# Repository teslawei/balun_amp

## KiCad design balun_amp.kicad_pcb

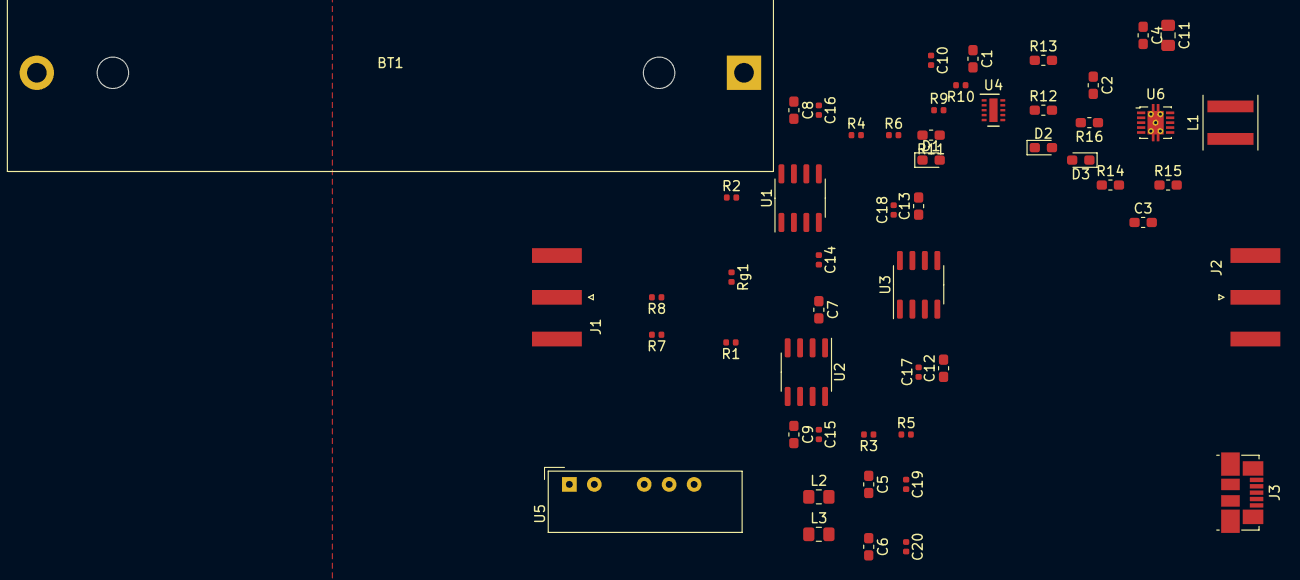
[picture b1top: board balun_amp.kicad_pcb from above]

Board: 4 copper layers, 53 parts (0 on the bottom side), 31 nets.

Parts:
BT1: Battery_Cell; BatteryHolder_MPD_BH-18650-PC2
C1, C2, C3, C5, C6: 10u; C_0603_1608Metric_Pad1.05x0.95mm_HandSolder
C4: 2.2u; C_0603_1608Metric_Pad1.05x0.95mm_HandSolder
C7, C8, C9, C12, C13: 1u; C_0603_1608Metric_Pad1.05x0.95mm_HandSolder
C10: 100n; C_0402_1005Metric
C11: 47u; C_0805_2012Metric_Pad1.15x1.40mm_HandSolder
C14, C15, C16, C17, C18, C19, C20: 10n; C_0402_1005Metric
D1, D2, D3: LED; LED_0603_1608Metric_Pad1.05x0.95mm_HandSolder
J1: Input; SMA_Amphenol_132289_EdgeMount
J2: Output; SMA_Amphenol_132289_EdgeMount
J3: USB_B_Micro; USB_Micro-B_Molex_47346-0001
L1: 6.8uH; L_Coilcraft_XAL5030
L2, L3: 150u; L_0805_2012Metric_Pad1.15x1.40mm_HandSolder
R1, R2, R3, R4, R5, R6, R7, R8: R; R_0402_1005Metric
R9: 2k; R_0402_1005Metric
R10: 1k; R_0402_1005Metric
R11, R13, R15, R16: 1.5k; R_0603_1608Metric_Pad1.05x0.95mm_HandSolder
R12: 10k; R_0603_1608Metric_Pad1.05x0.95mm_HandSolder
R14: 8.5k; R_0603_1608Metric_Pad1.05x0.95mm_HandSolder
Rg1: R; R_0402_1005Metric
U1, U2, U3: LT1226; SOIC-8_3.9x4.9mm_P1.27mm
U4: BQ2404x; WSON-10-1EP_2x3mm_P0.5mm_EP0.84x2.4mm
U5: NMA0512SC; Converter_DCDC_muRata_NMAxxxxSC_THT
U6: TPS61027; VSON-10-1EP_3x3mm_P0.5mm_EP1.65x2.4mm_ThermalVias

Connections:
+5V: C4.1, C11.1, R16.1, U5.1, U6.2
+BATT: BT1.1, C2.1, C3.1, D1.2, L1.1, R13.1, R14.1, U4.10, U6.1, U6.6
-BATT: BT1.2, C1.2, C2.2, C3.2, C4.2, C10.2, C11.2, J3.5, J3.6, R9.2, R10.2, R12.2, R15.2, U4.3, U4.6, U4.7, U5.2, U6.5, U6.8, U6.10
/VBUS: C1.1, C10.1, J3.1, U4.1
/VDD: C5.2, C8.2, C9.1, C13.1, C15.1, C16.2, C18.1, C19.2, L2.2, U1.7, U2.7, U3.7
/VSS: C6.1, C7.1, C12.2, C14.1, C17.2, C20.1, L3.2, U1.4, U2.4, U3.4
/input+: J1.1, R8.2
/input-: J1.2, R7.2
GND: C5.1, C6.2, C7.2, C8.1, C9.2, C12.1, C13.2, C14.2, C15.2, C16.1, C17.1, C18.2, C19.1, C20.2, J2.2, R5.1
unnamed: D1.1, R11.2
unnamed: D2.1, R13.2
unnamed: D2.2, U4.8
unnamed: D3.1, U6.4
unnamed: D3.2, R16.2
unnamed: J2.1, R6.1, U3.6
unnamed: L1.2, U6.9
unnamed: L2.1, U5.6
unnamed: L3.1, U5.4
unnamed: R1.1, R3.2, U2.6
unnamed: R1.2, Rg1.1, U2.2
unnamed: R2.1, Rg1.2, U1.2
unnamed: R2.2, R4.2, U1.6
unnamed: R3.1, R5.2, U3.3
unnamed: R4.1, R6.2, U3.2
unnamed: R7.1, U2.3
unnamed: R8.1, U1.3
unnamed: R9.1, U4.4
unnamed: R10.1, U4.2
unnamed: R11.1, U4.5
unnamed: R12.1, U4.9
unnamed: R14.2, R15.1, U6.7

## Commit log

2019-06-30 Initiate the diff amp design
2019-07-01 add 5v to +/-12V, add battery charger
2019-07-02 add 5v boost converter
2019-07-03 finish the draft schematic, generate the netlist and assign the footprint
2019-07-06 Update capacitor value and package
2019-07-08 no change
2019-07-15 Layout update
2019-07-15 Lib for the layout
2022-11-29 Rcapture the design
